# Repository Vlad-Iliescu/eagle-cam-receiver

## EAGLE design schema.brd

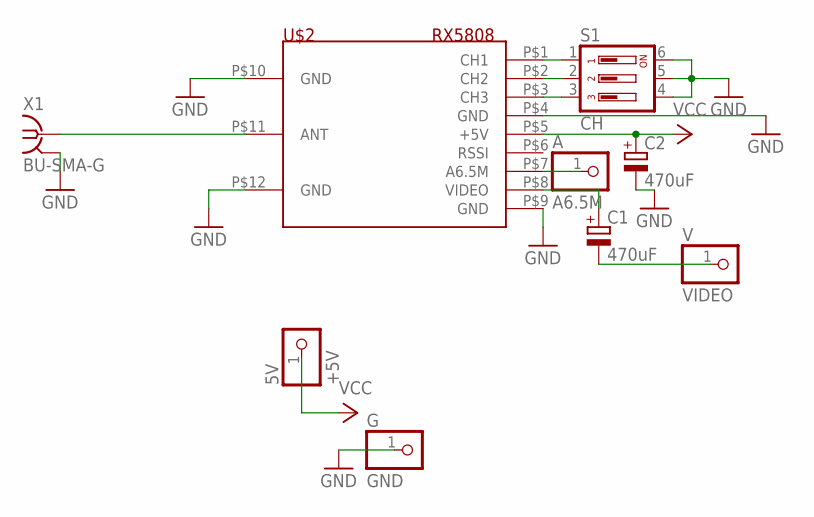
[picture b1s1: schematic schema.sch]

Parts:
5V: +5V; 1X01
A: A6.5M; 1X01
C1, C2: 470uF; E3,5-8
G: GND; 1X01
S1: CH; DS-03
U$2: RX5808
V: VIDEO; 1X01
X1: BU-SMA-G

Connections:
ANTENA: U$2.P$11 (ANT), X1.1
AUDIO: A.1, U$2.P$7 (A6.5M)
CH1: S1.1, U$2.P$1 (CH1)
CH2: S1.2, U$2.P$2 (CH2)
CH3: S1.3, U$2.P$3 (CH3)
GND: C2.-, G.1, S1.4, S1.5, S1.6, U$2.P$4 (GND), U$2.P$9 (GND), U$2.P$10 (GND), U$2.P$12 (GND), X1.2, X1.3 (2), X1.4 (2), X1.5 (2)
VCC: 5V.1, C2.+, U$2.P$5 (+5V)
VIDEO_IN: C1.+, U$2.P$8 (VIDEO)
VIDEO_OUT: C1.-, V.1

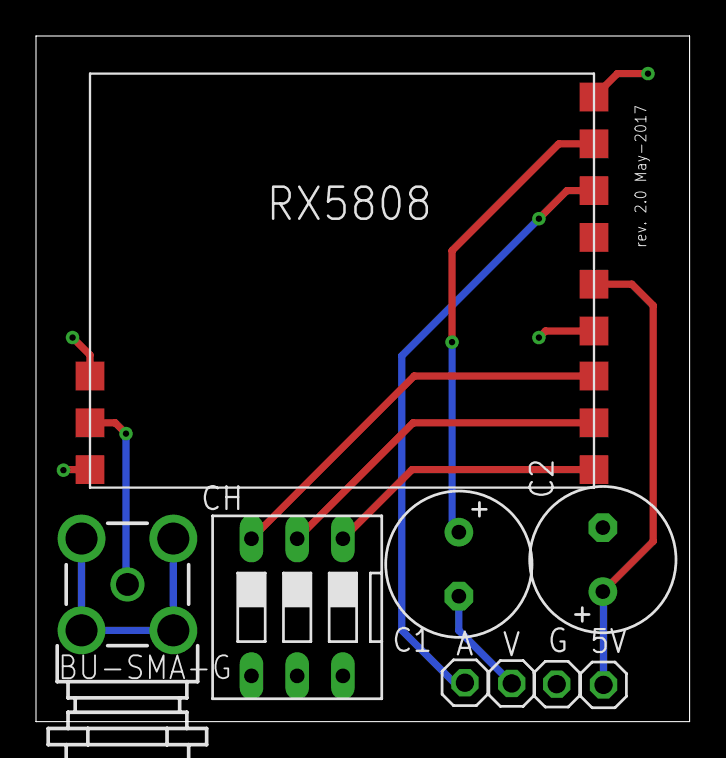
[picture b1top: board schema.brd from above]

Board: 2 copper layers, 36.3 x 38.1 mm, 9 parts (0 on the bottom side), 9 nets.

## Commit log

2017-04-06 Init
2017-04-12 added PDF schema
2017-05-30 Fixed pin switching issue and various
